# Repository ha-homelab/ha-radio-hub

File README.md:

# HA Radio Hub — MC2-D

**Three independent external antennas: Zigbee, Thread and Bluetooth.** MC2 keeps
a local classic-ESP32 Thread Border Router, Ember Zigbee coordinator, active BLE proxy,
Z-Wave, 433 MHz RF, LD2450 and BME680 behind one Ethernet uplink. Its
100 × 100 mm carrier holds finished modules with direct-solder male headers.

**[Open the public build guide](https://ha-homelab.github.io/ha-radio-hub/)** —
wiring lookup, assembly instructions and print/fabrication downloads.

**S1 prints the assembly guide on the board:** module outlines and roles,
connector signals, polarity, component values and a QR to the public guide.
The back carries a soldering checklist. [See both sides and the $0 incremental
artwork estimate](docs/pcb-silkscreen.md). Copper, holes, outline and component
compatibility are unchanged; the original fabrication archive is preserved.

*Generated from the current enclosure geometry with simplified electronic
bodies, including the pre-soldered XIAO ESP32C6 and the RECOM power assembly. Use the [full-hub CAD layout](mechanical/full-hub/layout.svg),
[print files](mechanical/full-hub/README.md) and [wiring guide](docs/full-hub-assembly.md)
for construction. Antennas and most cables are omitted for visibility; connect
the required antennas before operation.*

**Engineering prototype.** Source builds and CAD checks are not measurements of
coverage, power consumption, mechanical fit or radio certification. The
1,000 ft² house coverage target still requires testing.

## Start building

Follow [Start here](docs/start-here.md) for the ordered build, success checks,
Home Assistant connections and troubleshooting. Program the loose boards before
permanent assembly. The current hardware is **MC2-D + FH1**; older revisions are
kept as references.

For readable pages, searchable wiring and print downloads, clone or download
this repository and run from its root:

```sh
python3 tools/preview.py
```

This opens the local build guide in a browser; no Python packages are needed.
Alternatively, open [guide/index.html](guide/index.html) from the downloaded
folder. GitHub shows HTML source rather than running this guide. Use
`--port 0` if the default local port is occupied.

[Start here](docs/start-here.md) ·
[Versioned engineering build package](docs/releases.md) ·
[Print package — all STLs and quantities](mechanical/full-hub/FH1-MC2-D-PWR1-print-package.zip) ·
[Pin-to-pin harness CSV](hardware/external-antenna/harness.csv) ·
[Connection audit and I²C correction](docs/connection-audit.md) ·
[Documentation index](docs/README.md)

## Selected hardware

**Buying parts?** The [MC2 shopping guide](docs/mc2-shopping.md) gives quantities,
exact order codes, inspected AliExpress variants and outstanding availability
checks. **MC2-D uses XIAO ESP32C6 pre-soldered SKU 102010636** for Thread.
DigiKey showed 21 in stock at **$6.38** on 20 October 2026. The ESP32-DevKitC-VIE
is already ordered; do not buy another. Use the [PCB ordering record](docs/pcb-order.md)
for the new fabrication package and five-board prototype recommendation.
Buy factory-fitted headers wherever available. Two fine recovery leads on the
XIAO underside remain necessary; see the assembly instructions before soldering.

- **Espressif ESP32-DevKitC-VIE / ESP32-WROVER-IE:** previous-generation host
  with a factory external antenna connector, 8 MB flash and 8 MB physical PSRAM
  (4 MB directly addressable, quad 40 MHz); Ethernet host and active BLE 4.2 proxy.
- **Seeed XIAO ESP32C6 (Pre-Soldered), 102010636:** Thread RCP, 4 MB flash,
  native USB and factory 2×7 male headers. MC2-D firmware drives GPIO3 LOW and
  GPIO14 HIGH to select the external antenna. Two underside EN/BOOT wires to
  J10 preserve automatic recovery; a carrier service window makes them accessible.
- **Seeed XIAO MG24 (Pre-Soldered), 102010690:** Ember NCP with explicit
  external-antenna firmware and factory 2×7 male headers.
- **WIZnet WIZ850io:** shared-SPI Ethernet; retain the isolated PoE splitter and
  regulated low-voltage supply from the battery-fed PoE switch.
- **RECOM R-78K3.3-1.0:** the peripheral 5 V → 3.3 V converter, replacing
  Pololu D24V22F3. It connects to the existing J2 harness, with a local input
  capacitor and a removable mount. The power architecture is retained in MC2-D.
  [Power connections and limits](docs/full-hub-assembly.md#power-and-ethernet).
- **Three TE ANT-2.4-LCW-SMA antennas and three Taoglas CAB.618.E cables:**
  separate 50 Ω paths, standard SMA bulkheads, no combiner. The
  [updated selection](docs/pigtail-selection.md) saves $74.43 on three cables;
  use the **FH1-MC2-D-PWR1** enclosure and fit coupon.

Classic ESP32 retains the configured services and three active BLE connections,
but does not support BLE 5 extended advertising or Coded PHY. Lower power
consumption has not been established. See the [host migration](docs/classic-esp32-migration.md)
for the cost comparison, memory limits and compatibility checks.

The WK2132 bridge, ZAC93, band-matched CC1101/433.92 MHz antenna, radar,
environment sensor and power modules connect to the carrier by harnesses. The
[carrier BOM](hardware/external-antenna/cad/BOM.csv) and
[antenna BOM](hardware/external-antenna/rf-bom.json) accompany the assembly guide;
neither is a complete single-box shopping list on its own. The
[full assembly inventory](mechanical/full-hub/components.json) includes these
modules, the selected finished PoE splitter and the power/cable accessories.

The current carrier above is generated from native CAD. Historical AI surface-finish
concepts are kept in the [image record](hardware/external-antenna/images/README.md)
and are not assembly references for MC2-D.

*The two hand-soldered EN/BOOT leads supplement the factory headers.
[Exact test-pad and J10 diagram](hardware/external-antenna/cad/c6-recovery.svg) ·
[Assembly sequence](docs/full-hub-assembly.md#thread-recovery-leads).*

## Where the Z-Wave board and other parts go

**Zooz ZAC93 sits in its own removable insulated cradle beside the MC2-D
carrier.** Its underside 2×5 socket connects by a wired mating header to carrier
**J4**; the **DFR0627 / WK2132** bridge connects to **J3** and provides its serial
port. The ZAC93 does not plug into the ESP32 or a Raspberry Pi in this build.
Keep its stock antenna clear of straps, cables and metal.

*Current CAD assembly with simplified component bodies. Earlier AI appearance
concepts remain in the [historical image record](hardware/external-antenna/images/README.md);
use the current numbered CAD plan for module and cable placement.*

The **FH1 full-hub enclosure** has a 215 × 215 × 78 mm main shell, dedicated
mounts for the carrier, ZAC93, UART bridge, CC1101, PoE splitter and 3.3 V buck,
and a restrained DC-adapter/fuse tray. LD2450 mounts behind the room-facing lid
window. BME680 has a ventilated pod attached outside the warm shell with an air
gap. Three independent 2.4 GHz bulkheads remain on the fixed base.

[Exploded CAD and print files](mechanical/full-hub/README.md) ·
[Complete assembly and ZAC93 pin mapping](docs/full-hub-assembly.md) ·
[Graphical wiring](hardware/external-antenna/full-hub-wiring.svg)

## The smaller power assembly

The isolated PoE splitter supplies **5 V**. The **RECOM R-78K3.3-1.0** supplies
**3.3 V only to the peripherals**, through J2. Its 27 µF input capacitor and
insulated wire links fit on a 24 × 24 mm perfboard in the new **PWR1** holder.
Print the matching PWR1 base and holder together. No second custom PCB order
is needed. The converter and capacitor total **$4.38**, before shipping and tax,
versus $26.95 for the previous converter; see the dated [shopping record](docs/mc2-shopping.md).

[Power and capacitor wiring](hardware/external-antenna/power-wiring.svg) ·
[Perfboard: component and solder sides](hardware/external-antenna/power-perfboard.svg) ·
[Assembly and power checks](docs/full-hub-assembly.md#power-and-ethernet)

## Build and inspect

- [Native CAD, schematic and connector map](hardware/external-antenna/README.md).
- [Firmware builds and initial programming](firmware/external-antenna/README.md).
- [Browser USB installation for a privately built host image](docs/browser-flashing.md).
- [Verified-target network update workflow](firmware/external-antenna/updates/README.md).
- [Full-hub printable parts, component mounts and connector fit coupon](mechanical/full-hub/README.md).
- [Digital verification and remaining physical checks](hardware/external-antenna/validation.md).
- [RF commissioning procedure](docs/rf-commissioning.md) and
  [results sheet](hardware/external-antenna/coverage-results.csv).

## Optional ESP-NOW sensors

The [ESP-NOW profile](docs/espnow.md) adds remote sensor readings to the existing
MC2-D host without changing the carrier, wiring or enclosure. It reuses the
WROVER-IE's Bluetooth/Wi-Fi antenna; Ethernet carries the readings to Home
Assistant. The separate Thread and Zigbee radios keep their existing roles.

Included ESP32-C3 examples cover **BME280 temperature/humidity/pressure**, a
**DS18B20 temperature probe**, and a **door/window contact**. They use private
per-satellite keys, periodic state reports and hub freshness diagnostics. The
examples are continuously powered and updated over USB. This opt-in firmware
still needs physical coverage, power and simultaneous BLE/hub-load testing;
it does not establish battery life or motor-control safety.

[Build and configure ESP-NOW](firmware/espnow/README.md) ·
[Sensor wiring, use cases and commissioning](docs/espnow.md)

The largest print is 215 × 215 mm, within the selected TRONXY XY-3's nominal
310 × 310 × 330 mm print volume. The 65 mm adjacent antenna pitch and 150 mm
coax routes still require physical fit and coexistence tests. Module heights,
mating plugs, the existing CC1101 variant and printed tolerances must be checked
against the delivered hardware. Digital geometry checks do not establish
physical fit. The earlier [carrier-only enclosure](mechanical/module-carrier/external-antenna-prototype/README.md)
remains a historical option, not the full-hub housing.

MC2-A (S3) is preserved in a Git snapshot, and MC1 remains a regression target;
see the [engineering history](docs/design-history.md). MC1's Nano/H2 firmware,
16 MB partition table and compact enclosure do not fit MC2. The [design registry](hardware/designs.json) identifies the one active
revision. Do not mix images, pin maps or prices between revisions.

## Project information

Repository settings are managed by
[terraform-github-ha-homelab](https://github.com/4alvit/terraform-github-ha-homelab).
No private network keys, learned household RF codes or installation credentials
are distributed. See [infrastructure](docs/infrastructure.md),
[security](SECURITY.md), [license](LICENSE) and
[third-party notices](THIRD_PARTY_NOTICES.md).

Run `python3 tools/check.py` for offline document/source checks. Hardware,
firmware and mechanical guides list their reproducible validation commands.

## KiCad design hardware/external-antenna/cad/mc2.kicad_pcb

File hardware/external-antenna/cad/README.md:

# MC2-D classic ESP32 external-antenna carrier

**S1 assembly silkscreen:** [front/back previews and reproduction](../../../docs/pcb-silkscreen.md).
`silkscreen.py` adds ordinary white legends and the public-guide QR during
`finalize.py`. The electrical revision remains MC2-D. Run
`python3 silkscreen_check.py` to require exact non-silkscreen native equality
with the preceding board; clean reproduction also compares the artwork.

MC2 is a **100 × 100 mm, two-layer, all-through-hole engineering prototype**. All 19 fitted components face the room; two additional recovery footprints are unpopulated. There are no controller bodies above another component's solder tails and no carrier RF traces. Three independent factory RF connectors feed three external 2.4 GHz antennas through 50 Ω coax. This is a prototype fabrication candidate, not a production-qualified design or a claim of measured coverage.

**Power assembly:** J2 connects the offboard **RECOM R-78K3.3-1.0** plus its **27 µF input capacitor**. J2 remains a generic four-wire harness, not a regulator footprint. The native model now names RECOM; do not order the superseded Pololu. [Power design](../power-design.json) and [assembly guide](../../../docs/full-hub-assembly.md#power-and-ethernet).

## Exact controller boards

- **U1: Espressif ESP32-DevKitC-VIE**, with **ESP32-WROVER-IE**, 8 MB flash and 8 MB quad PSRAM (4 MB mapped into the host heap, configured at 40 MHz). This is the original dual-core ESP32 generation with an external antenna connector, not an S3 and not the no-PSRAM WROOM/32UE. It has **38 pins, two rows of 19**, 2.54 mm pitch and **25.40 mm row spacing**. The [official V4 dimension drawing](https://dl.espressif.com/dl/schematics/esp32_devkitc_v4_dimensions.pdf) gives a 27.94 × 48.26 mm carrier PCB with a projecting radio module. The official PCB layout overlays WROOM and longer WROVER outlines with the same 6.04 mm upper projection. Our body reservation includes that projection and rounding margin; the USB shell and RF center remain fit-check estimates. The [official ordering table](https://docs.espressif.com/projects/esp-dev-kits/en/latest/esp32/esp32-devkitc/user_guide.html#ordering-information) establishes the exact VIE memory/antenna variant. Do not substitute a generic 30-pin ESP32, WROVER-E with a PCB antenna, or an older 1.8 V WROVER module.
- **U2: Seeed Studio XIAO ESP32C6, pre-soldered SKU 102010636**, 4 MB flash. Buy this **factory-header** option, not bare SKU 113991254 or a three-pack. Two 1×7 rows at 2.54 mm pitch / 15.24 mm spacing replace the TinyC6 footprint. The board is nominally 21 × 17.8 mm, USB up. Native USB adds no competing UART bridge. [Manufacturer schematic and board](https://files.seeedstudio.com/wiki/SeeedStudio-XIAO-ESP32C6/XIAO_ESP32_C6_v1.0_SCH&PCB_260114.zip); [xiaoc6-evidence.json](xiaoc6-evidence.json) pins source hashes and geometry. **Factory headers do not expose EN or BOOT.** Two 30 AWG insulated leads from bottom **TP8/EN** and **TP2/BOOT** to J10 preserve automatic RCP flashing. This is the only required soldering to small pads on the finished C6 board; each pad is Ø1.143 mm. The carrier access window remains open from below after assembly. Use the MC2-D firmware: **GPIO3 LOW** powers the RF switch and **GPIO14 HIGH** selects U.FL before Thread starts. No battery is fitted.
- **U3: Seeed XIAO MG24, presoldered 102010690**. The module's U.FL RF path must be selected by the matching firmware: PB04 and PB05 high. A connected antenna alone does not switch the RF path. [Manufacturer board source](https://files.seeedstudio.com/wiki/XIAO_MG24/Getting_Start/XIAO_MG24_v1.0_KiCad_260114.zip).

All three use **U.FL / MHF1** mating coax, not MHF3 or MHF4. SMA bulkheads and antennas are offboard mechanical parts; their exact connector/gain/cable choices are in the [RF BOM](../rf-bom.json). No antenna is shared between radios.

## Electrical changes and connections

**I²C address correction (20 October 2026):** set the external DFR0627 DIP
switches **A1=1, A0=0**, with UART1 register/FIFO **0x50/0x51** and the entire
**0x50–0x57** block reserved. BME680 remains **0x77**. The old 1/1 setting
decoded **0x70–0x77**, including BME680's address. This correction changes
firmware and external switch setup, not carrier copper. See the
[connection audit](../../../docs/connection-audit.md).

[pin-plan.json](pin-plan.json) is the MC2-D firmware contract. All 21 application signals remain on the host: three native UARTs, shared hardware SPI, I²C, Ethernet IRQ/reset and C6 reset/boot. GPIO0 is reserved for recovery; GPIO1/3 remain on the factory USB-UART bridge; GPIO6–11 belong to flash and GPIO16/17 to PSRAM. GPIO34/35/36/39 are input-only and have no internal pull resistors. Runtime UART logging is disabled; the LD2450 UART0 is remapped to GPIO23 TX / GPIO18 RX after boot.

Host Thread TX/RX is **GPIO26 / GPIO36**, EN is GPIO27 and BOOT is GPIO15. XIAO carrier **pad8 / D7 / GPIO17** receives host TX; **pad7 / D6 / GPIO16** sends to host RX. Pad14 is diode-fed 5 V and pad13 is GND; pad12/local3V3 remains unconnected. **J10.1 goes to bottom TP8/EN; J10.2 goes to TP2/BOOT/GPIO9.** These are mandatory signal leads, not optional jumpers. GPIO8 already has the manufacturer's 5.1 kΩ pull-up and BOOT has 10 kΩ, so **R3 is removed** and no local C6 3.3 V rail is brought onto the carrier. Do not join the controller 3.3 V outputs to the peripheral rail.

Fit the two flexible 30 AWG leads before seating U2, with wire insulation diameter ≤0.8 mm and joint height ≤1.5 mm. Route them above the carrier between U2's two rows and out past the lower module edge to J10; the window is for solder/tool/inspection access, not a below-carrier cable route. Verify a module-to-carrier gap of at least 2.5 mm, apply strain relief to insulated wire with a small slack loop, and keep force off the gold pads. Do not attach the leads to the tiny top-side switches or battery pads. The 6 × 10.9 mm routed window has 1.5 mm corner radii. Check for shorts and pull-up continuity before power. A hot-air station is not needed; a fine iron tip, flux, magnification and small-pad soldering skill are required.

**R4 and R5 are required boot pull-downs, not optional parts.** R4 holds GPIO12 / SPI SCK LOW; the [WROVER-IE datasheet](https://www.espressif.com/sites/default/files/documentation/esp32-wrover-e_esp32-wrover-ie_datasheet_en.pdf), Table 2 and §4.2, specifies 3.3 V VDD_SDIO, selected by LOW on GPIO12/MTDI. R5 holds GPIO2 / SPI MOSI LOW so UART downloading works with GPIO0 LOW. Each resistor is 10 kΩ to GND. These two host outputs connect only to SPI slave inputs: never add a pull-up, LED, UART transmitter or other driving source to these nets. No eFuse modification is needed or assumed. The [WIZ850io v1.1 schematic](https://docs.wiznet.io/assets/files/wiz850io_sch_v110-3fcc19fc2acaf16f15c5f08f9c8330cb.pdf) has no SCK/MOSI pull-ups; its CS, IRQ and RESET already have 4.7 kΩ pull-ups. Verify the actual CC1101 module also has no conflicting SCK/MOSI pulls before assembly.

GPIO5 carries W5500 CS and is pulled HIGH by WIZ850io. GPIO15 carries C6 BOOT; LOW at host reset only suppresses the host ROM serial log, not normal flash boot. It is normally HIGH through the XIAO C6 board's boot pull-up and host default pull-up. Do not add cross-rail pull-ups. SPI uses the GPIO matrix at the configured device speeds; the W5500 runs at 10 MHz. The MG24 four-wire UART is GPIO32 TX / GPIO39 RX / GPIO33 RTS / GPIO14 CTS. CC1101 uses GPIO13 CS / GPIO25 GDO0 open-drain TX / GPIO35 GDO2 RX; I²C is GPIO21 SDA / GPIO22 SCL.

The original ESP32 radio supports **Bluetooth LE 4.2 legacy advertisements and connections**. The three active BLE proxy slots remain configured, but BLE5 extended advertisements, 2M PHY and Coded PHY are not supported. Zigbee and Thread still use their independent MG24 and C6 radios. A successful build does not establish runtime heap margin or simultaneous-load reliability.

The remaining external harnesses preserve MC1's function: J10 mandatory C6 recovery leads; J1 isolated/fused 5 V input; J2 offboard 3.3 V buck (current RECOM assembly override above); J3 DFR0627 UART expander; J4 ZAC93; J5 CC1101; J6 LD2450; J7 BME680. [Connectors and exact pad coordinates](connectors.json) and [net membership](../wiring.json) are generated from the same `design.py` as the native schematic and PCB. J8 is XIAO PC00-to-GND recovery; J9 is host GPIO0-to-GND recovery. Leave both unpopulated/open in operation.

The existing network PoE switch feeds an **active, isolated, regulated 5 V splitter** upstream of J1. Neither battery voltage nor raw PoE enters this board. J2 connects an external 3.3 V buck only to WIZ850io and peripheral harnesses. Controller 3.3 V outputs are **not joined** to that rail. **D1 is a 22 AWG insulated wire link, not a diode.** It preserves the original pad centers and directly feeds the host EXT_5V input without the avoidable Schottky drop ahead of its AMS1117. D2/D3 remain 1N5819: cathode/banded pad1 toward U2/U3, anode pad2 toward fused 5 V. Use two of the three purchased diodes and keep the third as a spare. Measure rail voltage at maximum simultaneous load: splitter, wire and contact losses still matter. **Never attach powered USB to the assembled hub**, even with PoE off: host USB can energize the complete 5 V bus through D1, and signal pins can backpower other rails. Flash loose boards first; assembled operation uses PoE and OTA only. Power down before connecting harnesses.

## Mechanical contract

`design.json` is the geometry authority. Four 2.7 mm NPTH holes are at (4,4), (96,4), (4,96), (96,96) mm, front-view origin at the top left. Use insulating M2.5 supports no wider than 5 mm at the PCB. The WIZ850io front-facing footprint is rotated180°: its RJ45 mouth is at y102 mm, x62.45–78.55 mm, 2 mm beyond the carrier. Support its jack with the enclosure cradle so cable insertion force does not rely on header joints.

The ledger retains physical USB shells, short USB service approaches and harness-mating envelopes. The XIAO C6 RF center is a **nominal manufacturer KiCad coordinate**, while the host and XIAO socket points remain **planning estimates**; use sufficient pigtail slack and verify engagement, bend radius and strain relief with delivered boards. Never press a mismatched miniature coax connector into place. Carrier fit, connector height, printer tolerances and simultaneous-radio performance remain unmeasured. [MC2 enclosure](../../../mechanical/full-hub/README.md).

## Checks and reproduction

Native ERC, DRC, unrouted items and schematic parity must all be **zero**; there are no intentional warning/overlap exemptions. The carrier has 31 connected nets. Its 38-pin host footprint is not compatible with the 44-pin MC2-A S3 footprint. MC2-D changes U2 to the 14-pin factory-header XIAO, removes R3, adds J10 and a real underside access window, and reroutes the copper Order the matching MC2-D board and firmware together; a zero-DRC result does not test the antenna switch or physical assembly. `test_design.py` also checks controller pin numbers, reserved GPIOs, supply separation and all module body/pad projections. Passive module symbols model connections, not the boards' internal power circuits.

Run with KiCad10's Python and libraries. Keep environment variables local to the task:

```sh
"$KICAD_PY" generate.py --libraries "$KICAD_LIBRARIES"
"$KICAD_CLI" sch export netlist --format kicadxml -o .build/mc2.xml mc2.kicad_sch
cp routing/mc2.ses .build/mc2.ses
"$KICAD_PY" finalize.py
"$KICAD_CLI" sch erc --severity-all --exit-code-violations --format json --output checks/erc.json mc2.kicad_sch
"$KICAD_CLI" pcb drc --severity-all --exit-code-violations --format json --schematic-parity --output checks/drc.json mc2.kicad_pcb
"$KICAD_PY" record_verification.py
python3 test_design.py
python3 render_assembly.py
python3 render_recovery.py
python3 reproduce_check.py --python "$KICAD_PY" --cli "$KICAD_CLI" --libraries "$KICAD_LIBRARIES"
```

The checked-in Specctra session was routed with Freerouting2.5.0, one optimization thread. It includes every connection, including J10 EN/BOOT and the host SPI boot pull-downs. Import it with `finalize.py`, which also refills ground. Track/via dimensions and clearance are unchanged from MC1: 0.25 mm signal, 0.80 mm power, 0.80/0.40 mm vias, 0.20 mm clearance and 0.50 mm copper-to-edge minimum. Fabrication settings are 1.6 mm FR-4, two 35 µm copper layers, green solder mask and lead-free HASL. This is a prototype fabrication package; it is not production qualified. The native KiCad board can be used for a small prototype after the BOM, power and assembly review; physical qualification then gates a larger run.

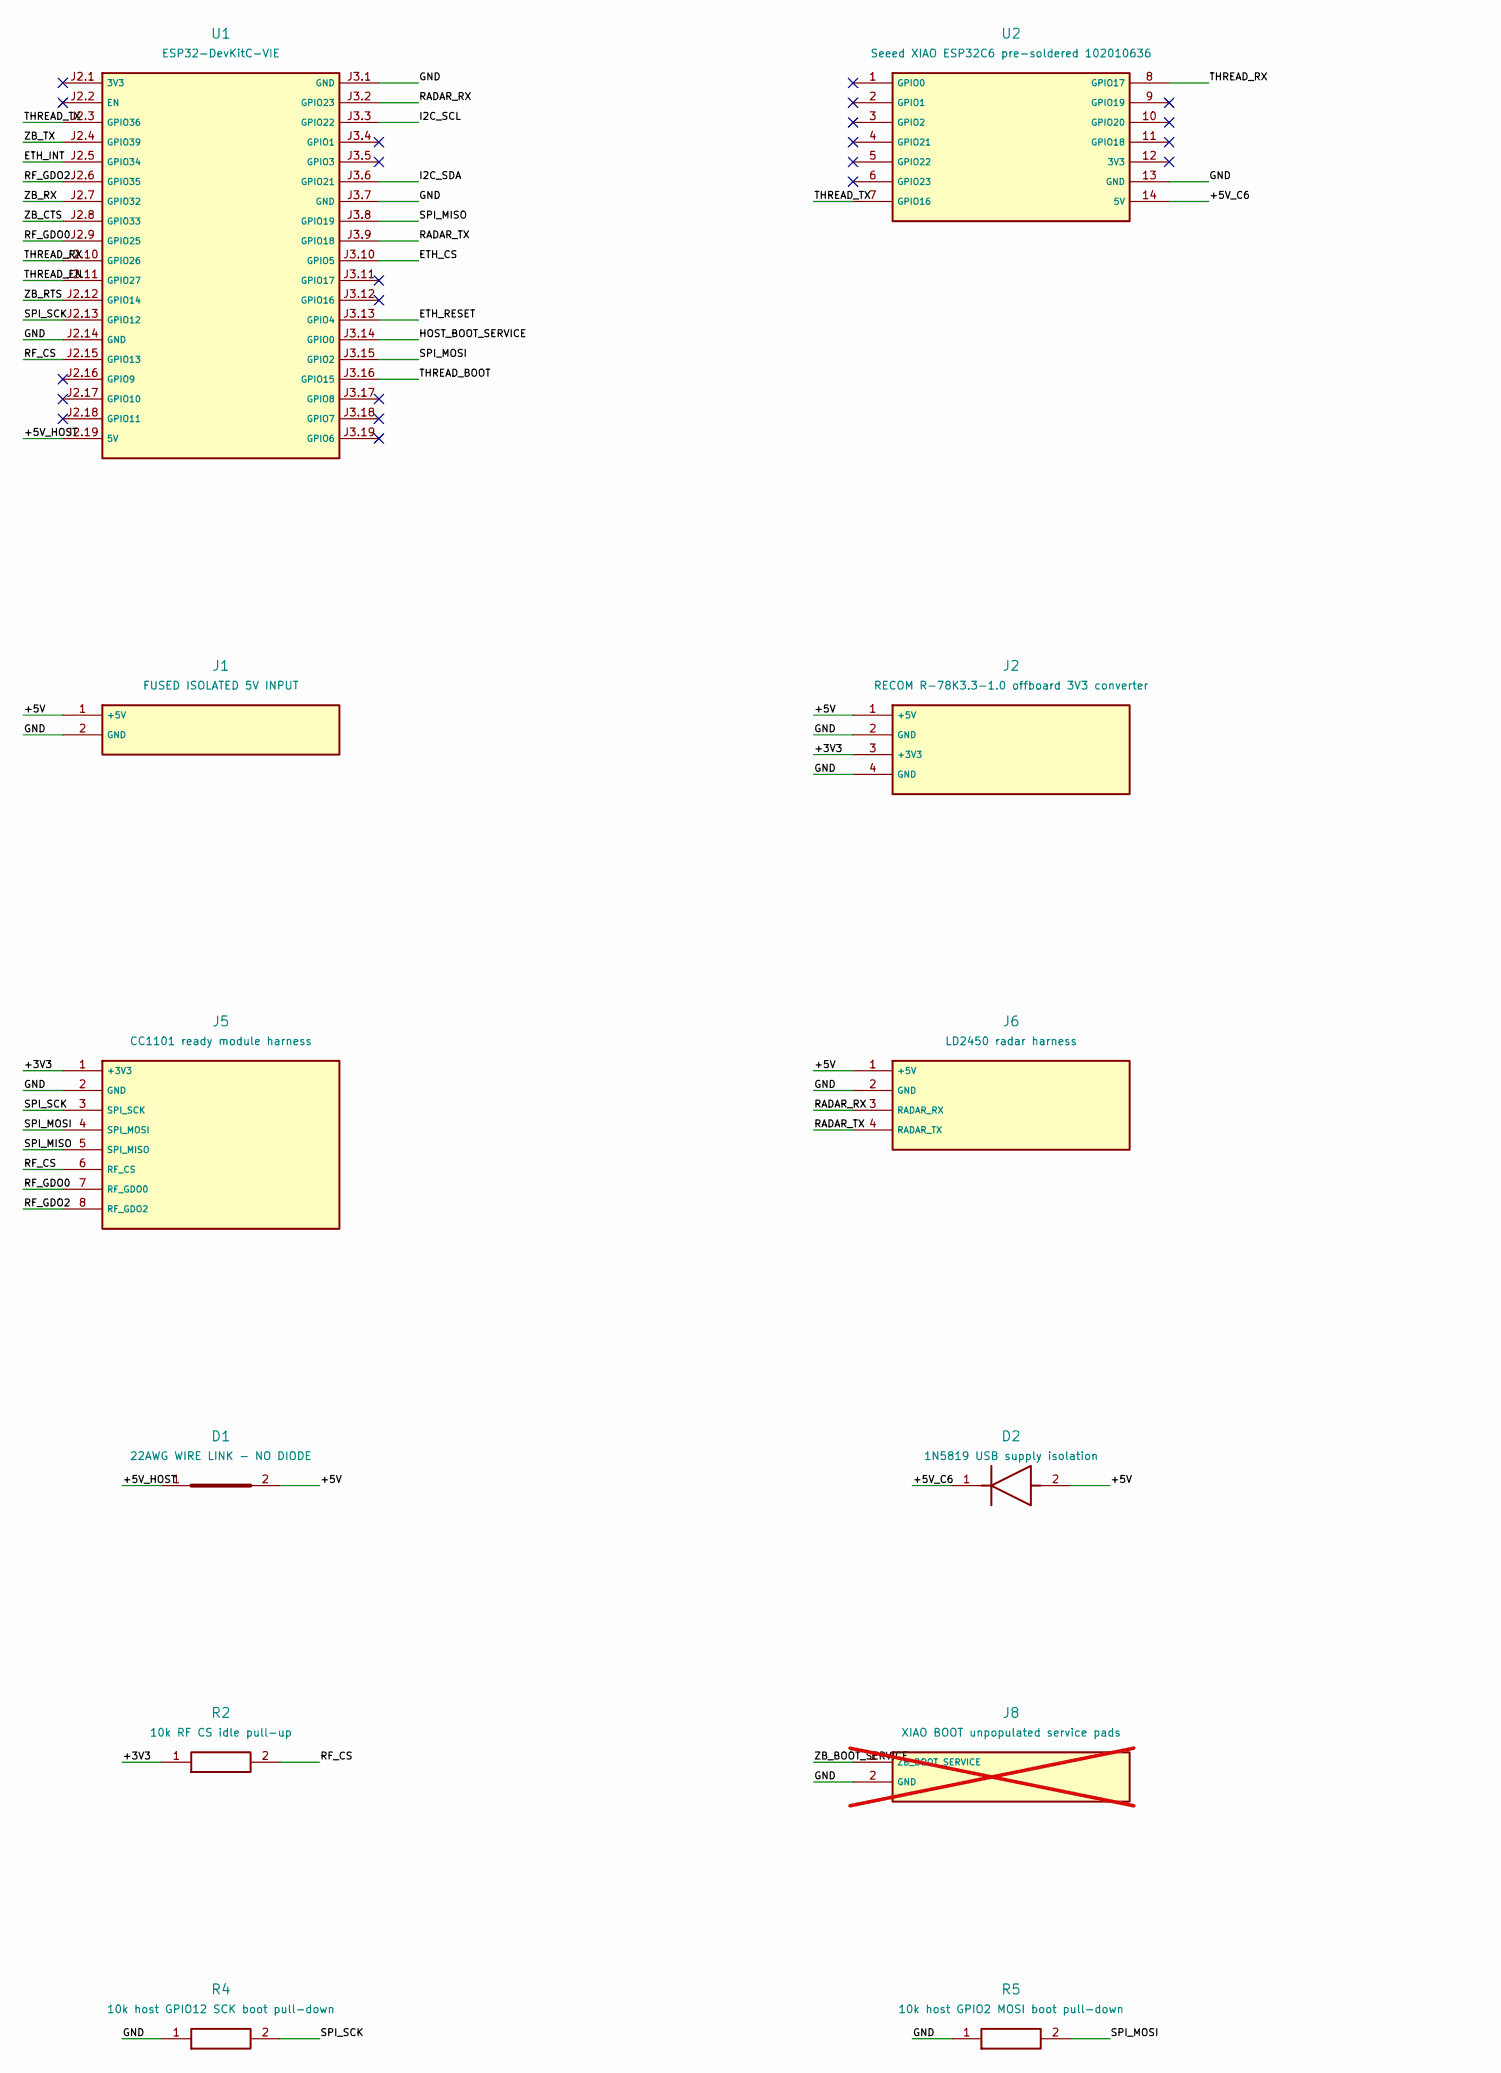
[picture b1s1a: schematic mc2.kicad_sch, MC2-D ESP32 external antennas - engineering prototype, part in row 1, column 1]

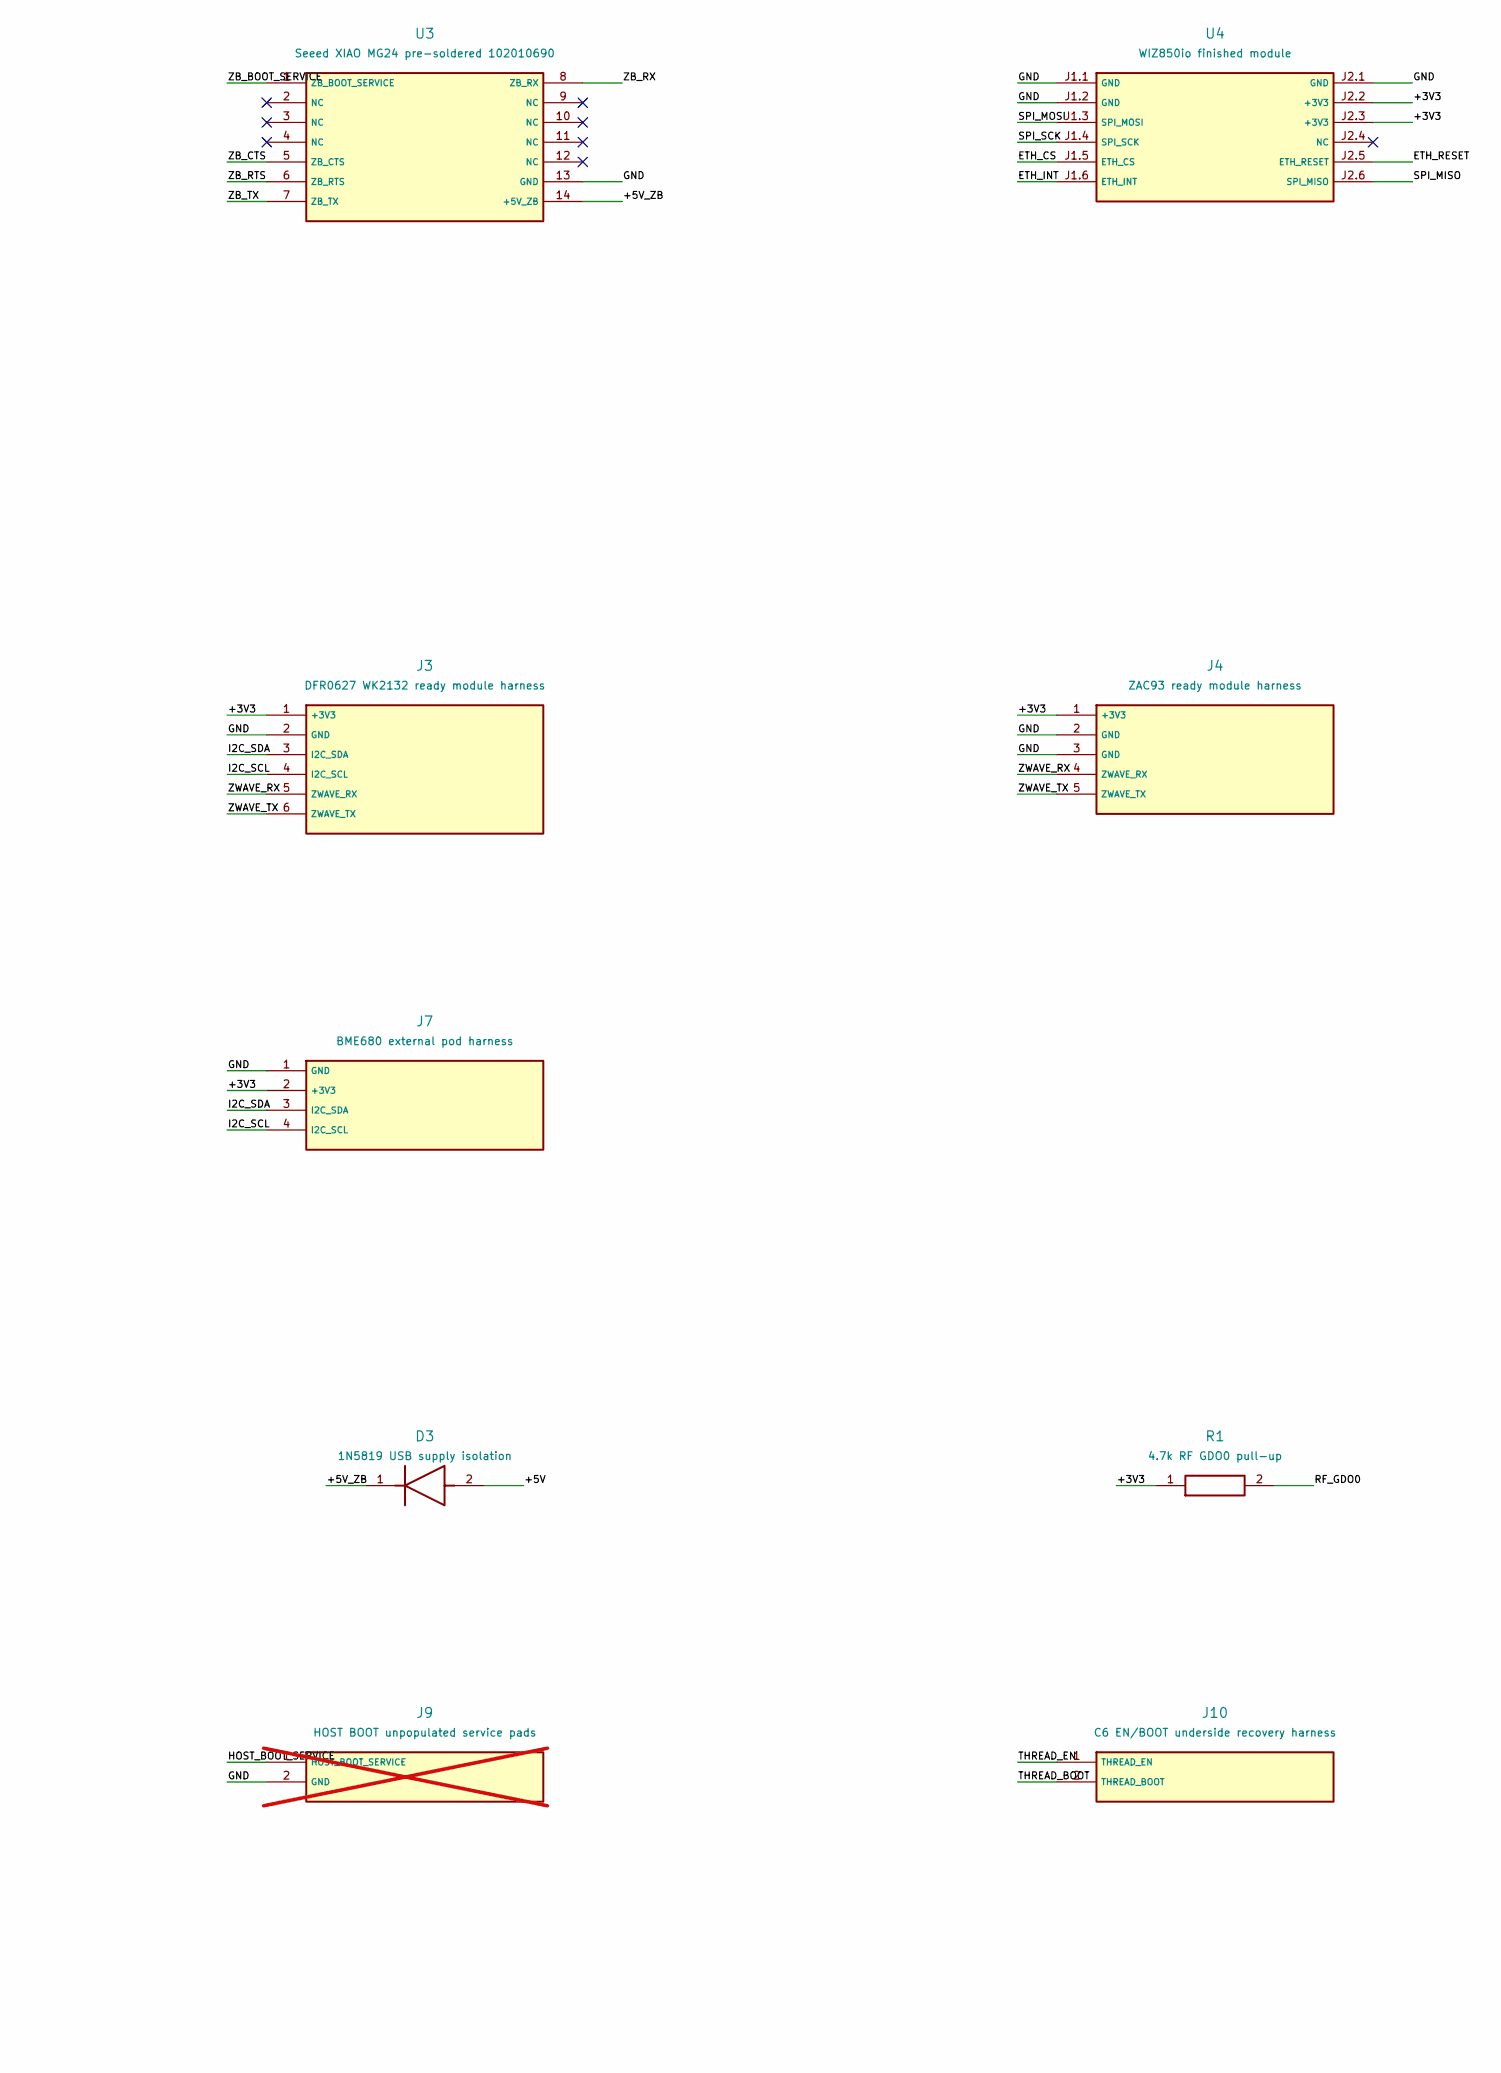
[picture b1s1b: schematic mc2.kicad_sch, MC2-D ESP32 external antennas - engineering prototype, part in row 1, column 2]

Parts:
D1: 22AWG WIRE LINK - NO DIODE; Wire_Link_P7.62mm
D2, D3: 1N5819 USB supply isolation; D_DO-41_SOD81_P7.62mm_Horizontal
J1: FUSED ISOLATED 5V INPUT; PinHeader_1x02_P2.54mm_Vertical
J2: RECOM R-78K3.3-1.0 offboard 3V3 converter; PinHeader_1x04_P2.54mm_Vertical
J3: DFR0627 WK2132 ready module harness; PinHeader_1x06_P2.54mm_Vertical
J4: ZAC93 ready module harness; PinHeader_1x05_P2.54mm_Vertical
J5: CC1101 ready module harness; PinHeader_1x08_P2.54mm_Vertical
J6: LD2450 radar harness; PinHeader_1x04_P2.54mm_Vertical
J7: BME680 external pod harness; PinHeader_1x04_P2.54mm_Vertical
J8: XIAO BOOT unpopulated service pads; PinHeader_1x02_P2.54mm_Vertical; not fitted
J9: HOST BOOT unpopulated service pads; PinHeader_1x02_P2.54mm_Vertical; not fitted
J10: C6 EN/BOOT underside recovery harness; PinHeader_1x02_P2.54mm_Vertical
R1: 4.7k RF GDO0 pull-up; R_Axial_DIN0207_L6.3mm_D2.5mm_P7.62mm_Horizontal
R2: 10k RF CS idle pull-up; R_Axial_DIN0207_L6.3mm_D2.5mm_P7.62mm_Horizontal
R4: 10k host GPIO12 SCK boot pull-down; R_Axial_DIN0207_L6.3mm_D2.5mm_P7.62mm_Horizontal
R5: 10k host GPIO2 MOSI boot pull-down; R_Axial_DIN0207_L6.3mm_D2.5mm_P7.62mm_Horizontal
U1: ESP32-DevKitC-VIE; ESP32_DevKitC_VIE
U2: Seeed XIAO ESP32C6 pre-soldered 102010636; XIAO_ESP32C6
U3: Seeed XIAO MG24 pre-soldered 102010690; XIAO_MG24
U4: WIZ850io finished module; WIZ850io

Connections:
/+3V3: J2.3 (+3V3), J3.1 (+3V3), J4.1 (+3V3), J5.1 (+3V3), J7.2 (+3V3), R1.1, R2.1, U4.J2.2 (+3V3), U4.J2.3 (+3V3)
/+5V: D1.2, D2.2, D3.2, J1.1 (+5V), J2.1 (+5V), J6.1 (+5V)
/+5V_C6: D2.1, U2.14 (5V)
/+5V_HOST: D1.1, U1.J2.19 (5V)
/+5V_ZB: D3.1, U3.14 (+5V_ZB)
/ETH_CS: U1.J3.10 (GPIO5), U4.J1.5 (ETH_CS)
/ETH_INT: U1.J2.5 (GPIO34), U4.J1.6 (ETH_INT)
/ETH_RESET: U1.J3.13 (GPIO4), U4.J2.5 (ETH_RESET)
/GND: J1.2 (GND), J2.2 (GND), J2.4 (GND), J3.2 (GND), J4.2 (GND), J4.3 (GND), J5.2 (GND), J6.2 (GND), J7.1 (GND), J8.2 (GND), J9.2 (GND), R4.1, R5.1, U1.J2.14 (GND), U1.J3.1 (GND), U1.J3.7 (GND), U2.13 (GND), U3.13 (GND), U4.J1.1 (GND), U4.J1.2 (GND), U4.J2.1 (GND)
/HOST_BOOT_SERVICE: J9.1 (HOST_BOOT_SERVICE), U1.J3.14 (GPIO0)
/I2C_SCL: J3.4 (I2C_SCL), J7.4 (I2C_SCL), U1.J3.3 (GPIO22)
/I2C_SDA: J3.3 (I2C_SDA), J7.3 (I2C_SDA), U1.J3.6 (GPIO21)
/RADAR_RX: J6.3 (RADAR_RX), U1.J3.2 (GPIO23)
/RADAR_TX: J6.4 (RADAR_TX), U1.J3.9 (GPIO18)
/RF_CS: J5.6 (RF_CS), R2.2, U1.J2.15 (GPIO13)
/RF_GDO0: J5.7 (RF_GDO0), R1.2, U1.J2.9 (GPIO25)
/RF_GDO2: J5.8 (RF_GDO2), U1.J2.6 (GPIO35)
/SPI_MISO: J5.5 (SPI_MISO), U1.J3.8 (GPIO19), U4.J2.6 (SPI_MISO)
/SPI_MOSI: J5.4 (SPI_MOSI), R5.2, U1.J3.15 (GPIO2), U4.J1.3 (SPI_MOSI)
/SPI_SCK: J5.3 (SPI_SCK), R4.2, U1.J2.13 (GPIO12), U4.J1.4 (SPI_SCK)
/THREAD_BOOT: J10.2 (THREAD_BOOT), U1.J3.16 (GPIO15)
/THREAD_EN: J10.1 (THREAD_EN), U1.J2.11 (GPIO27)
/THREAD_RX: U1.J2.10 (GPIO26), U2.8 (GPIO17)
/THREAD_TX: U1.J2.3 (GPIO36), U2.7 (GPIO16)
/ZB_BOOT_SERVICE: J8.1 (ZB_BOOT_SERVICE), U3.1 (ZB_BOOT_SERVICE)
/ZB_CTS: U1.J2.8 (GPIO33), U3.5 (ZB_CTS)
/ZB_RTS: U1.J2.12 (GPIO14), U3.6 (ZB_RTS)
/ZB_RX: U1.J2.7 (GPIO32), U3.8 (ZB_RX)
/ZB_TX: U1.J2.4 (GPIO39), U3.7 (ZB_TX)
/ZWAVE_RX: J3.5 (ZWAVE_RX), J4.4 (ZWAVE_RX)
/ZWAVE_TX: J3.6 (ZWAVE_TX), J4.5 (ZWAVE_TX)

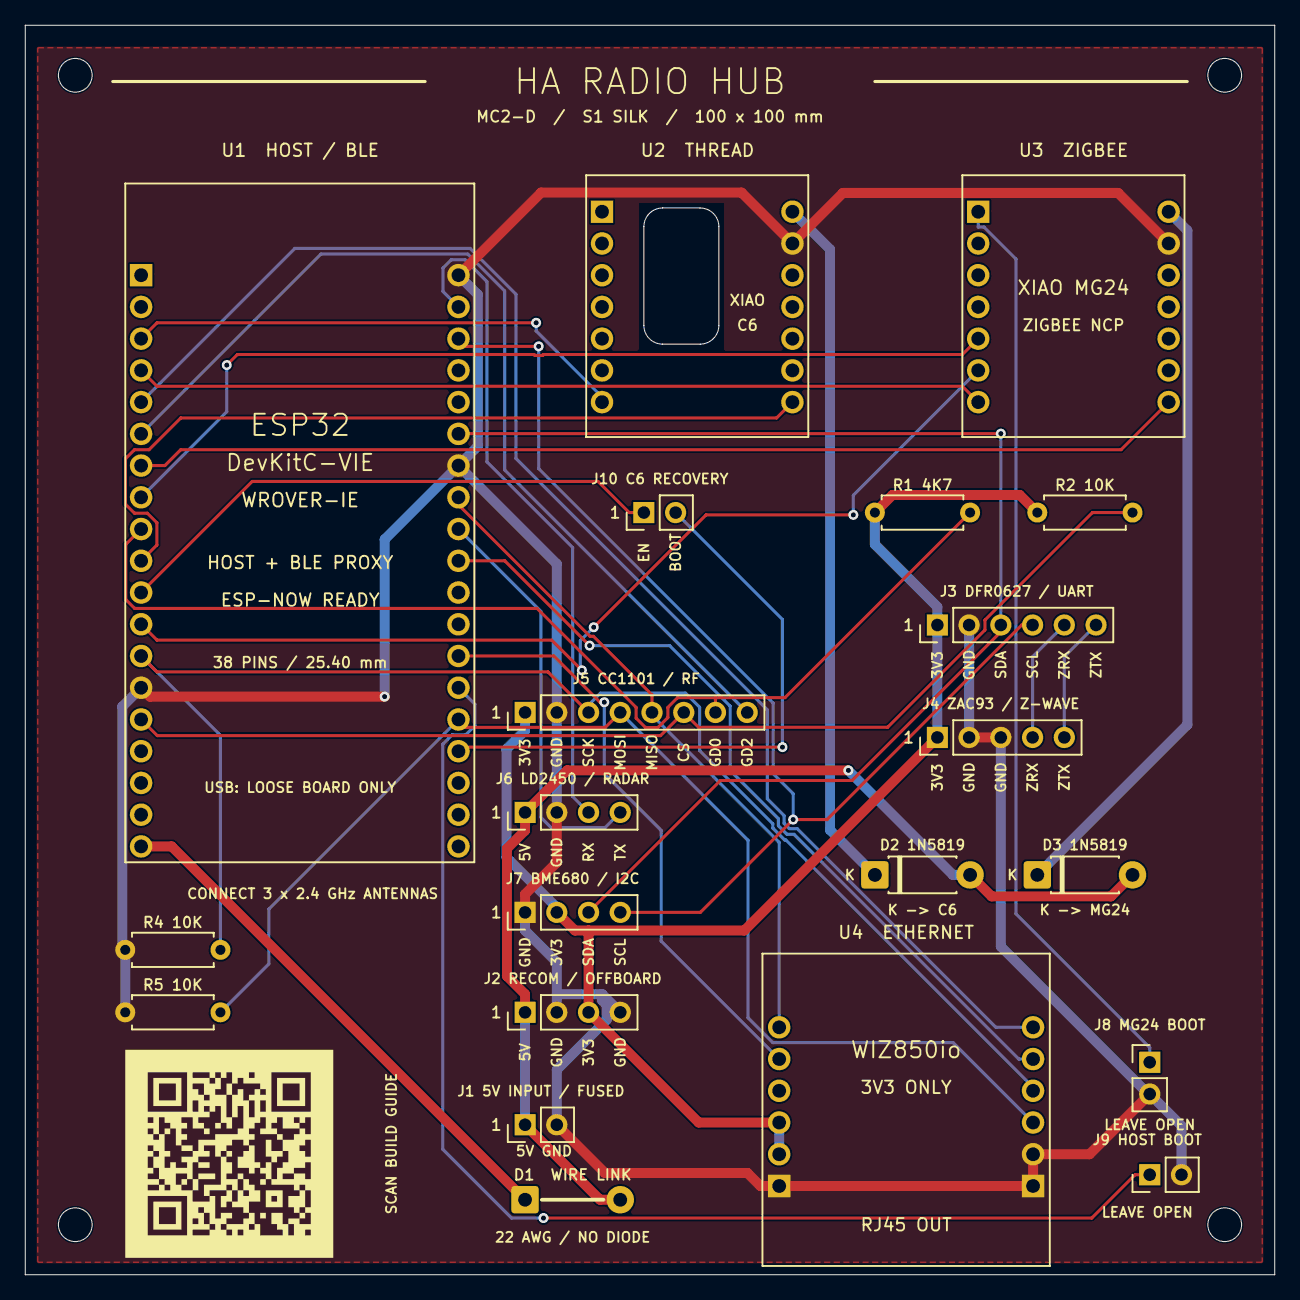
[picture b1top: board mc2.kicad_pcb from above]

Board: 2 copper layers, 100.0 x 100.0 mm, 25 parts (0 on the bottom side), 31 nets.

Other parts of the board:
H1, H2, H3, H4: M2.5 NYLON NPTH

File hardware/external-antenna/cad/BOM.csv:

Reference,Quantity,Fitted,Part / module,Carrier footprint,Side,Assembly note,Source
U1,1,true,ESP32-DevKitC-VIE,MC2:ESP32_DevKitC_VIE,Front,"Factory male pins; WROVER-IE external U.FL; 8MB flash/8MB quad PSRAM; 5V via D1 wire link (NO DIODE); GPIO0 boot,1/3 USB-UART,6-11 flash,16/17 PSRAM reserved; BLE4.2, no BLE5 extended advertising",https://docs.espressif.com/projects/esp-dev-kits/en/latest/e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
U2,1,true,Seeed XIAO ESP32C6 pre-soldered 102010636,MC2:XIAO_ESP32C6,Front,Factory 2x7 male headers; native USB; ROM RX17/D7 TX16/D6; bottom TP8 EN and TP2 BOOT9 require J10 flying leads; onboard GPIO8 pullup; GPIO3 LOW and GPIO14 HIGH select external U.FL; no battery,https://wiki.seeedstudio.com/xiao_esp32c6_getting_started/
U3,1,true,Seeed XIAO MG24 pre-soldered 102010690,MC2:XIAO_MG24,Front,External UART PC06/PC07; CTS PC04 RTS PC05; USB probe preserved; 3V3 OUT NC; external U.FL selected by firmware PB04=1 PB05=1,https://files.seeedstudio.com/wiki/XIAO_MG24/Getting_Start/X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
U4,1,true,WIZ850io finished module,MC2:WIZ850io,Front,Direct factory pins; two1x6 at20.32 rowspacing; RJ45 faces BOTTOM with mouth y=102mm; NO PoE extraction;3.3V only,https://docs.wiznet.io/img/products/wiz850io/wiz850io_dimension.png
J1,1,true,FUSED ISOLATED 5V INPUT,MC2:PinHeader_1x02_P2.54mm_Vertical,Front,Offboard assembled active PoE splitter and fused 5V harness. No raw PoE voltage on carrier.,https://www.samtec.com/products/tsw
J2,1,true,RECOM R-78K3.3-1.0 offboard 3V3 converter,MC2:PinHeader_1x04_P2.54mm_Vertical,Front,Harness interface only; pin1 buckVIN; pin2GND;pin3buckVOUT;pin4GND. RECOM plus 27uF input capacitor stays on supported offboard perfboard.,https://www.samtec.com/products/tsw
J3,1,true,DFR0627 WK2132 ready module harness,MC2:PinHeader_1x06_P2.54mm_Vertical,Front,"Harness to DFR0627 I2C and UART1, no WK2132 SMD on carrier. J3.5=module TX1;J3.6=module RX1; IA1=1 IA0=0; register address 0x50, FIFO 0x51; reserve 0x50-0x57; BME680 remains 0x77; verify physical markings.",https://wiki.dfrobot.com/dfr0627
J4,1,true,ZAC93 ready module harness,MC2:PinHeader_1x05_P2.54mm_Vertical,Front,Carrier1->ZACpin1;2->pin6;3->pin9;4->pin8RX;5->pin10TX. Different from ZAC physical header layout.,https://www.samtec.com/products/tsw
J5,1,true,CC1101 ready module harness,MC2:PinHeader_1x08_P2.54mm_Vertical,Front,3.3V; GDO0 open-drain TX with external4.7k pullup; GDO2 receiver.,https://www.samtec.com/products/tsw
J6,1,true,LD2450 radar harness,MC2:PinHeader_1x04_P2.54mm_Vertical,Front,Carrier3->radarRX;carrier4<-radarTX;5V supply;3.3V data.,https://www.samtec.com/products/tsw
J7,1,true,BME680 external pod harness,MC2:PinHeader_1x04_P2.54mm_Vertical,Front,"External pod,1GND2VDD3SDA4SCL;I2C pullups on modules;do notaddunreviewedpullups.",https://www.samtec.com/products/tsw
D1,1,true,22AWG WIRE LINK - NO DIODE,MC2:Wire_Link_P7.62mm,Front,"Legacy D1 location: fit insulated 22AWG wire, not a diode. Pad1 to host EXT_5V, pad2 to fused5V. Host USB would energize the whole bus: flash loose, then use PoE and OTA only.",https://dl.espressif.com/dl/schematics/esp32_devkitc_v4-sch.pdf
D2,1,true,1N5819 USB supply isolation,MC2:D_DO-41_SOD81_P7.62mm_Horizontal,Front,Cathodepad1->board5V;anodepad2->fused5Vbus. VerifyUSBprogrammingpowerpaths;forwarddropheadroom.,https://www.vishay.com/docs/88525/1n5817.pdf
D3,1,true,1N5819 USB supply isolation,MC2:D_DO-41_SOD81_P7.62mm_Horizontal,Front,Cathodepad1->board5V;anodepad2->fused5Vbus. VerifyUSBprogrammingpowerpaths;forwarddropheadroom.,https://www.vishay.com/docs/88525/1n5817.pdf
R1,1,true,4.7k RF GDO0 pull-up,MC2:R_Axial_DIN0207_L6.3mm_D2.5mm_P7.62mm_Horizontal,Front,,https://www.vishay.com/docs/28729/mrs16.pdf
R2,1,true,10k RF CS idle pull-up,MC2:R_Axial_DIN0207_L6.3mm_D2.5mm_P7.62mm_Horizontal,Front,,https://www.vishay.com/docs/28729/mrs16.pdf
J8,0,false,XIAO BOOT unpopulated service pads,MC2:PinHeader_1x02_P2.54mm_Vertical,Front,Temporary short D0/PC00 to GND while resetting XIAO for recovery. Normally OPEN.,https://www.samtec.com/products/tsw
J9,0,false,HOST BOOT unpopulated service pads,MC2:PinHeader_1x02_P2.54mm_Vertical,Front,Normally OPEN; short GPIO0 to GND while pressing host RESET for USB-UART ROM recovery.,https://www.samtec.com/products/tsw
J10,1,true,C6 EN/BOOT underside recovery harness,MC2:PinHeader_1x02_P2.54mm_Vertical,Front,Two 30AWG insulated leads above carrier under module; window for access: J10.1->XIAO TP8 EN; J10.2->TP2 BOOT/GPIO9. Required for host reset and automatic RCP flashing. Fit before module seating; retain slack and strain relief.,https://www.samtec.com/products/tsw
R4,1,true,10k host GPIO12 SCK boot pull-down,MC2:R_Axial_DIN0207_L6.3mm_D2.5mm_P7.62mm_Horizontal,Front,Required LOW at reset: WROVER-IE VDD_SDIO=3.3V; WIZ850io and CC1101 SCK are inputs without pull-ups.,https://www.vishay.com/docs/28729/mrs16.pdf
R5,1,true,10k host GPIO2 MOSI boot pull-down,MC2:R_Axial_DIN0207_L6.3mm_D2.5mm_P7.62mm_Horizontal,Front,Required LOW for serial download with GPIO0=LOW; MOSI connects only to SPI slave inputs.,https://www.vishay.com/docs/28729/mrs16.pdf
